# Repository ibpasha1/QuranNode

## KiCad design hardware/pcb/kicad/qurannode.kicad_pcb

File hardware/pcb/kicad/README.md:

# QuranNode mainboard — KiCad project

KiCad 8 project. Two things are pre-generated so you skip grunt work:
- **Board outline + placement** from the enclosure (single source of truth).
- **A connected netlist** (`qurannode.net`, via SKiDL) — import it to drop all
  footprints + a ratsnest onto the board, so you place & route instead of drawing
  the whole schematic first.

| File | What |
|------|------|
| `qurannode.kicad_pro` | KiCad project (open this) |
| `qurannode.kicad_pcb` | Board with **Edge.Cuts outline + placement labels** baked in |
| `qurannode.kicad_sch` | Schematic stub (draw here if you prefer schematic-first) |
| `qurannode.net` | **KiCad netlist** — 79 parts, 70 nets (Pcbnew → Import Netlist) |
| `gen_netlist.py` | SKiDL source for the netlist (edit here, re-run to regenerate) |
| `PINOUT-VERIFY.md` | ⚠️ **IC pin-number checklist — read before routing** |
| `qurannode-outline.dxf` | Board outline as DXF — reliable Edge.Cuts import path |
| `placement.md` | Connector/component X/Y in board coordinates |
| `gen_board_outline.py` | Regenerates the outline/DXF/placement from enclosure params |

Board: **62.8 × 150 mm**, 2 mm corner radius (inner cavity 64 × 151.2 − 0.6 mm/side).

## ⚠️ Read `PINOUT-VERIFY.md` first
The netlist's **connectivity is validated** (no dangling nets) and passive pin numbers
are correct, but **IC package pin numbers are best-effort** and must be checked against
each datasheet/symbol — a wrong number wires a net to the wrong pad. The checklist
tells you exactly what to confirm.

## Fast path: import the netlist
1. Open `qurannode.kicad_pcb` (already has the outline + placement guides). It looks
   like an empty board of the right size — correct; components come from step 2.
2. **Pcbnew → File → Import → Netlist…** → select `qurannode.net` →
   **"Load and Test Netlist"** (reports footprint errors) → **"Update PCB"**. KiCad
   places all 79 footprints (in a pile) with the full ratsnest.
   - Footprint errors on the first pass are normal: fix any string KiCad can't resolve
     to your installed libs / chosen MPN (strings are in `gen_netlist.py`).
3. Verify pinouts per `PINOUT-VERIFY.md`, then **place** parts to the `placement.md`
   positions and **route**.

## Regenerating the netlist (SKiDL)
```sh
python3 -m venv .venv && . .venv/bin/activate && pip install skidl
python3 gen_netlist.py     # -> qurannode.net
```
Edit connections/parts in `gen_netlist.py` (one place), re-run, re-import.
(`.venv/`, SKiDL `*_sklib.py`/`*.erc`/`*.log` are git-ignored.)

## ⚠️ Honest status
- KiCad was **not installed here to validate** these files. The `.kicad_pcb`/`.kicad_sch`
  are best-effort KiCad-8 format. **If either won't open**, use the DXF path below —
  the outline geometry is correct regardless of the s-expression wrapper.
- The schematic is **not** auto-wired. A hand-generated wired schematic can't reliably
  land wires on symbol pins, so I didn't fake one — capture it from `../netlist.md`.

## If the .kicad_pcb won't open (DXF fallback)
1. New KiCad project → open the empty PCB.
2. **File → Import → Graphics…** → `qurannode-outline.dxf` → place on **Edge.Cuts**,
   scale 1:1, mm. That gives you the exact board outline.
3. Use `placement.md` to drop connectors on the right edges/positions.

## Workflow from here
1. **Schematic** (`qurannode.kicad_sch`): draw sheets Power → MCU → Audio → Display →
   SD → Nav from `../netlist.md`. Pull IC symbols from a **verified library**
   (SnapEDA / the JLCPCB library), not by hand — the netlist connects by pin *name*.
2. **Footprints:** assign per `../BOM.csv`; match the exact MPN footprints for the
   hand-soldered connectors. INMP441 needs its **bottom acoustic-port** footprint.
3. **Annotate → ERC → Update PCB from Schematic** — pulls the netlist into
   `qurannode.kicad_pcb`, which already has the outline + placement guides.
4. **Place & route** per `../DESIGN.md` (regulator loop, audio isolation, USB pair,
   WROOM antenna keep-out, mic hole under the lid grille).
5. **Fab/assembly export:** JLCPCB fabrication toolkit plugin → Gerbers + BOM + CPL.
   Mark hand-soldered parts so they're excluded from the SMT placement file.

## Regenerating the outline
`python3 gen_board_outline.py` — re-derives the outline if the enclosure changes.
**This overwrites `qurannode.kicad_pcb`**, so once you've started real layout, don't
rerun it; instead re-import the refreshed `qurannode-outline.dxf` onto Edge.Cuts.

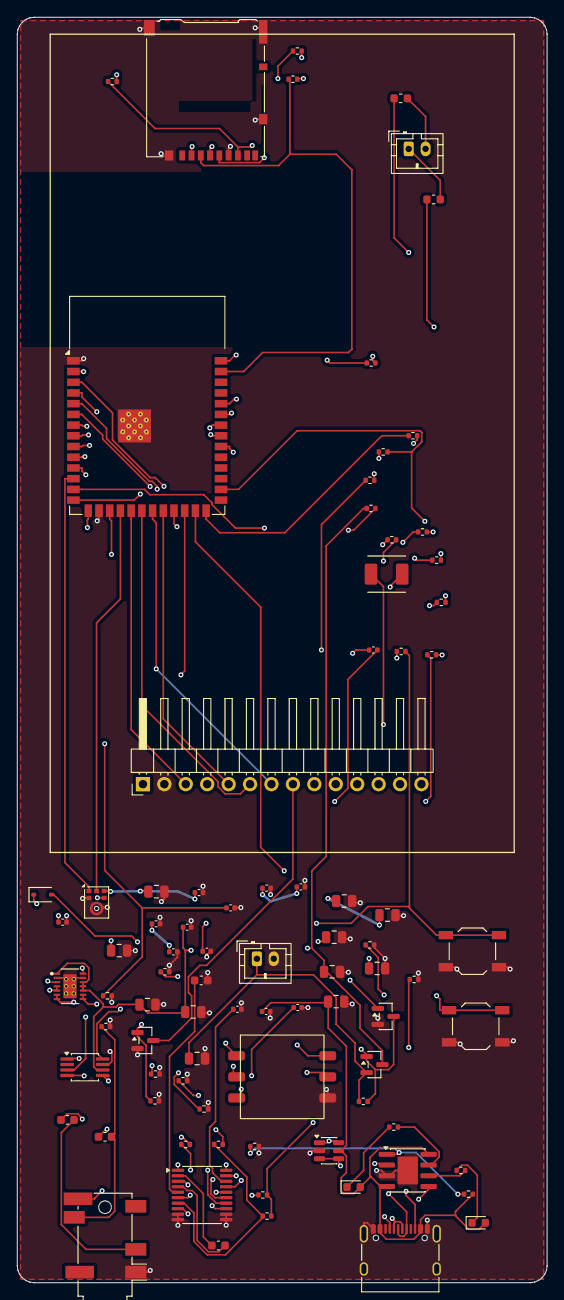
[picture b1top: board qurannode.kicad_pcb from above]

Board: 4 copper layers, 62.8 x 150.0 mm, 85 parts (0 on the bottom side), 70 nets.

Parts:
C1, C9, C11, C12, C13, C14, C24, C25, C28: 100n; C_0402_1005Metric
C2, C3, C4, C5, C15, C23, C26, C27: 10u; C_0805_2012Metric
C6, C7, C8: 22u; C_0805_2012Metric
C10, C16: 1u; C_0402_1005Metric
C17, C18, C19, C20: 2u2; C_0603_1608Metric
C21, C22: 470n; C_0402_1005Metric
D1: BAT54; D_SOD-323
D2: red; LED_0603_1608Metric
D3: grn; LED_0603_1608Metric
FB1, FB2: 600R; L_0603_1608Metric
J1: USB-C-16P; USB_C_Receptacle_XKB_U262-16XN-4BVC11
J2: microSD; microSD_HC_Hirose_DM3AT-SF-PEJM5
J3: LCD_HDR_1x14; PinHeader_1x14_P2.54mm_Horizontal
J4: SPK_JST_PH2; JST_PH_B2B-PH-K_1x02_P2.00mm_Vertical
J5: BATT_JST_PH2; JST_PH_B2B-PH-K_1x02_P2.00mm_Vertical
J6: TRS_3.5; Jack_3.5mm_PJ31060-I_Horizontal
L1: 1u5; MWSA0402S
MK1: ICS-43434; InvenSense_ICS-43434-6_3.5x2.65mm
Q1: 2N7002; SOT-23
Q2: AO3401A_PFET; SOT-23
Q3: 2N7002_NFET; SOT-23
R1, R2: 5k1; R_0402_1005Metric
R3: 1k2; R_0402_1005Metric
R4, R5, R9, R14, R15, R18, R29, R30, R31, R32: 10k; R_0402_1005Metric
R6, R7: 1k; R_0402_1005Metric
R8, R10, R12, R13, R16, R17, R21, R25: 100k; R_0402_1005Metric
R11: 560k; R_0402_1005Metric
R19, R20, R28: 100R; R_0402_1005Metric
R22, R23, R24: 20k; R_0402_1005Metric
R26, R27: 4k7; R_0402_1005Metric
SW1: NAV_5WAY; NAV_5WAY_SMD
SW2: RST; SW_SPST_TL3342
SW3: BOOT; SW_SPST_TL3342
U1: ESP32-S3-WROOM-1
U2: PCM5102A; TSSOP-20_4.4x6.5mm_P0.65mm
U3: PAM8302A; MSOP-8_3x3mm_P0.65mm
U4: TP4056; SOIC-8-1EP_3.9x4.9mm_P1.27mm_EP2.41x3.3mm
U5: TPS63020; TPS63020_DSJ_VSON14
U6: USBLC6-2SC6; SOT-23-6

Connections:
+3V3: C6.1, C7.1, C8.1, C9.1, C12.1, C13.1, C14.1, C15.1, C25.1, C26.1, C27.1, C28.1, J2.4, J3.1, MK1.5, R11.1, R13.2, R14.1, R15.1, R18.2, R21.2, R26.2, R27.2, R30.2, R31.2, R32.2, U1.2, U2.1, U2.8, U2.20, U5.4, U5.5
AIN: C21.1, R23.2, R24.2
AMP_EN: R25.1, U1.11, U3.1
BL_G: Q1.1, R28.2, R29.1
CHG_CHRG: R6.2, U4.7
CHG_STBY: R7.2, U4.6
DISP_BL: R28.1, U1.8
DISP_CLK: J3.7, U1.21
DISP_CS: J3.3, U1.19
DISP_DC: J3.5, U1.22
DISP_MOSI: J3.6, U1.20
DISP_RST: J3.4, J3.11, U1.23
EN: C10.1, R14.2, SW2.1, U1.3
GND: C1.2, C2.2, C3.2, C4.2, C5.2, C6.2, C7.2, C8.2, C9.2, C10.2, C11.2, C12.2, C13.2, C14.2, C15.2, C16.2, C17.2, C22.2, C23.2, C24.2, C25.2, C26.2, C27.2, C28.2, J1.A1, J1.A12, J1.B1, J1.B12, J1.SH, J2.6, J2.SH, J3.2, J5.2, J6.S, MK1.2, MK1.3, Q1.2, Q3.2, R1.2, R2.2, R3.2, R5.2, R10.2, R12.2, R17.2, R22.2, R25.2, R29.2, SW1.6, SW2.2, SW3.2, U1.1, U1.16, U1.41, U2.3, U2.9, U2.10, U2.11, U2.12, U2.16, U2.19, U3.7, U4.3, U4.9, U5.2, U5.13, U5.15, U6.2
HOLD_G: Q3.1, R9.2, R10.1
HP_DET: J6.TN, R21.1, U1.17
HP_L: C19.2, J6.T, R22.1
HP_R: C20.2, J6.R1
I2S_BCK: U1.4, U2.13
I2S_DATA: U1.6, U2.14
I2S_WS: U1.5, U2.15
IO0: R15.2, SW3.1, U1.28
MIC_SCK: MK1.4, U1.7
MIC_SD: MK1.6, U1.18
MIC_WS: MK1.1, U1.12
unnamed: J1.A5, R1.1
unnamed: J1.B5, R2.1
unnamed: R3.1, U4.2
unnamed: R4.1, R5.1, U4.1
unnamed: D2.1, R6.1
unnamed: D3.1, R7.1
unnamed: L1.1, U5.8, U5.9
unnamed: L1.2, U5.6, U5.7
unnamed: R11.2, R12.1, U5.3
unnamed: C16.1, U2.18
unnamed: C17.1, U2.5
unnamed: C18.1, U2.2
unnamed: C18.2, U2.4
unnamed: R18.1, U2.17
unnamed: C19.1, R19.2
unnamed: C20.1, R20.2
unnamed: C21.2, U3.3
unnamed: C22.1, U3.4
unnamed: FB1.1, U3.5
unnamed: FB2.1, U3.8
unnamed: J3.8, Q1.3
NAV_DN: SW1.2, U1.33
NAV_L: SW1.3, U1.32
NAV_MID: D1.1, SW1.5, U1.24
NAV_R: SW1.4, U1.25
NAV_UP: SW1.1, U1.34
OUTL: R19.1, R23.1, U2.6
OUTR: R20.1, R24.1, U2.7
PG: R13.1, U5.14
PWR_G: D1.2, Q2.1, Q3.3, R8.2
PWR_HOLD: R9.1, U1.26
SD_CLK: J2.5, U1.36
SD_CS: J2.2, R30.1, U1.40
SD_MISO: J2.7, R32.1, U1.35
SD_MOSI: J2.3, R31.1, U1.39
SPK_N: FB2.2, J4.2
SPK_P: FB1.2, J4.1
TOUCH_SCL: J3.10, R27.1, U1.10
TOUCH_SDA: J3.12, R26.1, U1.9
USB_DM: J1.A7, J1.B7, U1.13, U6.3, U6.4
USB_DP: J1.A6, J1.B6, U1.14, U6.1, U6.6
VBAT: C3.1, J5.1, Q2.2, R8.1, U4.5
VBAT_SENSE: C11.1, R16.2, R17.1, U1.15
VBUS: C1.1, C2.1, D2.2, D3.2, J1.A4, J1.A9, J1.B4, J1.B9, R4.2, U4.4, U4.8, U6.5
VSYS: C4.1, C5.1, C23.1, C24.1, Q2.3, R16.1, U3.6, U5.1, U5.10, U5.11, U5.12

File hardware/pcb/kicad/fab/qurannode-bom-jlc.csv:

Comment,Designator,Footprint,LCSC Part #
100n,"C1,C9,C11,C12,C13,C14,C24,C25,C28",C0402,C1525
10u,"C2,C3,C4,C5,C15,C23,C26,C27",C0805,C15850
22u,"C6,C7,C8",C0805,C45783
1u,"C10,C16",C0402,C52923
2u2,"C17,C18,C19,C20",C0603,C23630
470n,"C21,C22",C0402,C471404
BAT54,D1,SOD-323,C86299
red,D2,LED0603,C2286
grn,D3,LED0603,C12624
600R,"FB1,FB2",L0603,C97000
USB-C-16P,J1,USB-C-16P,C319148
microSD,J2,microSD-DM3AT,C114218
TRS_3.5,J6,PJ-31060,C2939583
1u5,L1,MWSA0402S,C408334
ICS-43434,MK1,ICS-43434-6_3.5x2.65,C5656610
2N7002,"Q1,Q3",SOT-23,C8545
AO3401A,Q2,SOT-23,C15127
5k1,"R1,R2",R0402,C25905
1k2,R3,R0402,C25749
10k,"R4,R5,R9,R14,R15,R18,R29,R30,R31,R32",R0402,C25744
1k,"R6,R7",R0402,C11702
100k,"R8,R10,R12,R13,R16,R17,R21,R25",R0402,C25741
560k,R11,R0402,C227139
100R,"R19,R20,R28",R0402,C25076
20k,"R22,R23,R24",R0402,C25765
4k7,"R26,R27",R0402,C25900
ESP32-S3-WROOM-1,U1,ESP32-S3-WROOM-1,C2913202
PCM5102A,U2,TSSOP-20,C107671
PAM8302A,U3,MSOP-8,C113367
TP4056,U4,SOIC-8-EP,C382139
TPS63020,U5,VSON-14-DSJ,C15483
USBLC6-2SC6,U6,SOT-23-6,C7519
